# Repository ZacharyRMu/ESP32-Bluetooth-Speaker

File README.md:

# ESP32 Bluetooth Speaker with Controls

A DIY Bluetooth speaker project using an ESP32 microcontroller, a MAX98357A I²S DAC amplifier, and control buttons. Stream audio via Bluetooth A2DP, and control playback, track navigation, and volume directly from buttons.

---

## Table of Contents

- [Features](#features)  
- [Hardware Requirements](#hardware-requirements)  
- [Circuit / Wiring](#circuit--wiring)  
- [Software & Libraries](#software--libraries)  
- [Usage](#usage)  
- [Troubleshooting](#troubleshooting)  
- [Optional Enhancements](#optional-enhancements)  
- [Project Structure](#project-structure)  
- [License](#license)

---

## Features

- Bluetooth A2DP audio streaming from any compatible device (phone, computer, etc.)  
- Physical controls: play/pause, next/previous track, volume up/down  
- Uses I²S interface with MAX98357A amplifier for better audio quality  
- Configurable and extensible (add LEDs, battery, enclosures, etc.)

---

## Hardware Requirements

| Component | Description / Notes |
|---|---|
| ESP32 board | Any variant that supports Bluetooth + I²S; power via USB or external supply |
| MAX98357A I²S amplifier module | To convert digital audio to analog and drive the speaker |
| Speaker | 4 Ω or 8 Ω, approx. 3 W recommended |
| Push-buttons (×5) | For Play/Pause, Next Track, Previous Track, Volume Up, Volume Down |
| Jumper wires | For connections between ESP32, amplifier, buttons |
| Capacitor (10 µF, optional) | Between VIN and GND of amplifier to smooth power & reduce noise |
| Micro-USB cable | To program and power the ESP32 |
| Enclosure (optional) | To house the electronics nicely and safely |

---

## Circuit / Wiring

**Connections:**

- **Power**  
  - VIN on ESP32 → VIN on MAX98357A  
  - GND → GND (common ground)

- **I²S Audio Signals**  
  - I²S_BCLK (bit clock) → GPIO 27  
  - I²S_LRC (word select / left-right clock) → GPIO 14  
  - I²S_DIN (audio data) → GPIO 26  

- **Buttons** (one side of each button to GND; the other to the ESP32 GPIO pins)  
  - Play/Pause → GPIO 5  
  - Previous Track → GPIO 18  
  - Next Track → GPIO 19  
  - Volume Up → GPIO 21  
  - Volume Down → GPIO 22  

- **Optional components**  
  - 10 µF capacitor between VIN & GND at the amplifier module (reduces noise)  
  - If using amplifier shutdown / gain pins, connect per the datasheet or leave floating if unused

---

## Software & Libraries

- **Arduino IDE / PlatformIO**  
- Required libraries:  
  - [ESP32-A2DP](https://github.com/pschatzmann/ESP32-A2DP) — for Bluetooth audio sink  
  - [Arduino-Audio-Tools](https://github.com/pschatzmann/arduino-audio-tools) — for I²S & audio stream handling  

**Basic flow:**  
1. Initialize I²S stream with the given pins  
2. Start Bluetooth A2DP sink (set device name, default volume)  
3. In main loop, poll buttons with debounce logic  
4. On button presses, issue commands: play/pause, next, previous, volume up/down  

---

## Usage

1. Clone this repository.  
2. Install required libraries (Arduino IDE library manager / PlatformIO, or clone directly).  
3. Connect hardware per wiring instructions.  
4. Upload the code to the ESP32.  
5. Power it up.  
6. On your phone/computer, pair with Bluetooth device named **“ESPEAKER”** (default).  
7. Play audio and use the buttons to control playback and volume.  

---

## Troubleshooting

| Issue | Possible Cause | Solution |
|---|---|---|
| No audio / speaker silent | Wiring error; amplifier VIN not powered; ground not common | Double-check wiring; ensure amplifier module is powered; verify I²S pins match code |
| Distorted or noisy audio | Voltage supply noisy; missing capacitor; gain too high | Add the 10 µF capacitor; check amplifier gain settings; use a clean power supply |
| Buttons not responding | Wrong pins; no pull-ups; bouncing | Make sure button pins match code; use `INPUT_PULLUP` mode; implement debounce |
| BLE not pairing / not visible | Device name wrong; Bluetooth not started; power issues | Confirm `a2dp_sink.start("ESPEAKER")` runs; check ESP32’s Bluetooth functionality |

---

## Optional Enhancements

- Add battery power (for portability), e.g. LiPo + charging circuit (e.g., TP4056)  
- Enclosure: 3D-printed, wooden box, repurposed case  
- Status LEDs: indicate pairing, connected, playing state  
- RGB LEDs synced to music for visual effects  
---

## License

Specify your license here. For example: MIT License — see [LICENSE](LICENSE) file.

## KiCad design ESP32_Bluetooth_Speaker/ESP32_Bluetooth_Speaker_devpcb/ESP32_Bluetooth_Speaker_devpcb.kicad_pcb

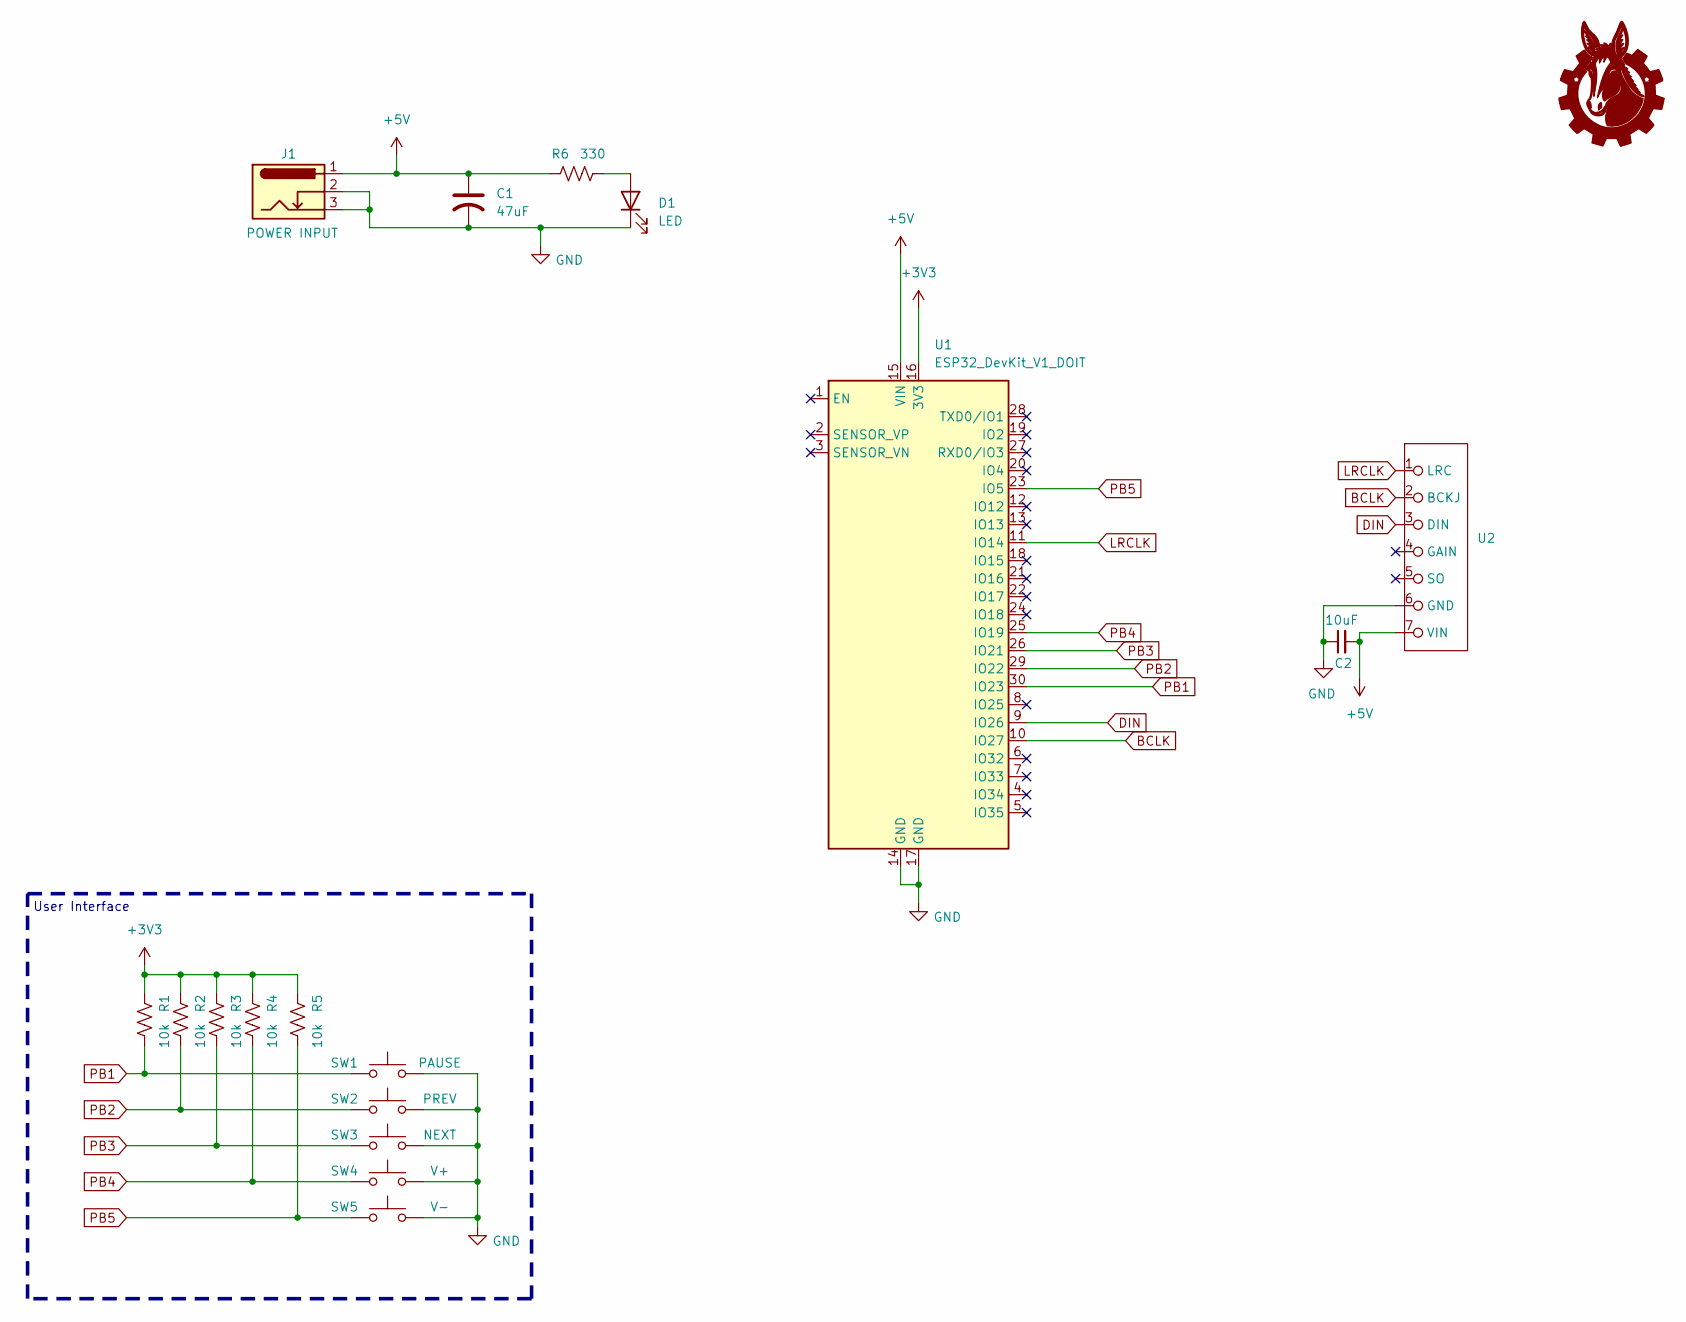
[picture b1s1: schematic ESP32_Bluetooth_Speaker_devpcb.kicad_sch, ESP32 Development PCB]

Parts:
C1: 47uF; CP_Radial_D6.3mm_P2.50mm
C2: 10uF; CP_Radial_D6.3mm_P2.50mm
D1: LED; LED_D5.0mm
J1: POWER INPUT; BarrelJack_CUI_PJ-102AH_Horizontal
R1, R2, R3, R4, R5: 10k; R_Axial_DIN0207_L6.3mm_D2.5mm_P7.62mm_Horizontal
R6: 330; R_Axial_DIN0207_L6.3mm_D2.5mm_P7.62mm_Horizontal
SW1: PAUSE; SW_Tactile_SPST_Angled_PTS645Vx58-2LFS
SW2: PREV; SW_Tactile_SPST_Angled_PTS645Vx58-2LFS
SW3: NEXT; SW_Tactile_SPST_Angled_PTS645Vx58-2LFS
SW4: V+; SW_Tactile_SPST_Angled_PTS645Vx58-2LFS
SW5: V-; SW_Tactile_SPST_Angled_PTS645Vx58-2LFS
U1: ESP32_DevKit_V1_DOIT; esp32_devkit_v1_doit
U2: PinSocket_1x07_P2.54mm_Vertical

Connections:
+3V3: R1.2, R2.2, R3.2, R4.2, R5.2, U1.16 (3V3)
+5V: C1.1, C2.2, J1.1, R6.2, U1.15 (VIN), U2.7 (VIN)
BCLK: U1.10 (IO27), U2.2 (BCKJ)
DIN: U1.9 (IO26), U2.3 (DIN)
GND: C1.2, C2.1, D1.1 (K), J1.2, J1.3, SW1.2, SW2.2, SW3.2, SW4.2, SW5.2, U1.14 (GND), U1.17 (GND), U2.6 (GND)
LRCLK: U1.11 (IO14), U2.1 (LRC)
unnamed: D1.2 (A), R6.1
PB1: R1.1, SW1.1, U1.30 (IO23)
PB2: R2.1, SW2.1, U1.29 (IO22)
PB3: R3.1, SW3.1, U1.26 (IO21)
PB4: R4.1, SW4.1, U1.25 (IO19)
PB5: R5.1, SW5.1, U1.23 (IO5)

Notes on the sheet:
User Interface

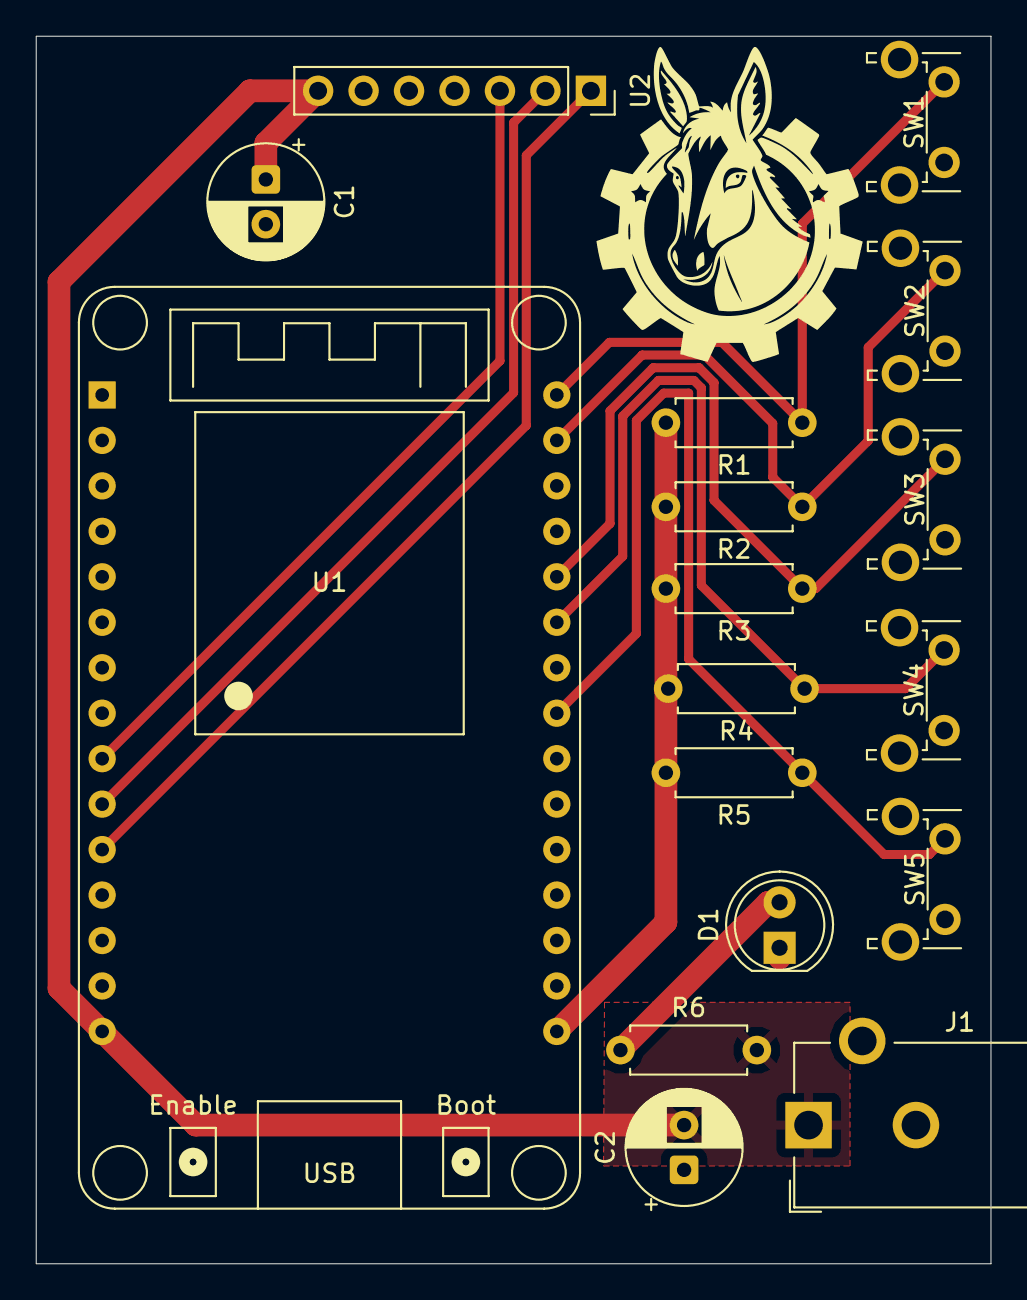
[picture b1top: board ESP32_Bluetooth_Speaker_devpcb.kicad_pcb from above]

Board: 2 copper layers, 53.3 x 68.6 mm, 17 parts (0 on the bottom side), 12 nets.

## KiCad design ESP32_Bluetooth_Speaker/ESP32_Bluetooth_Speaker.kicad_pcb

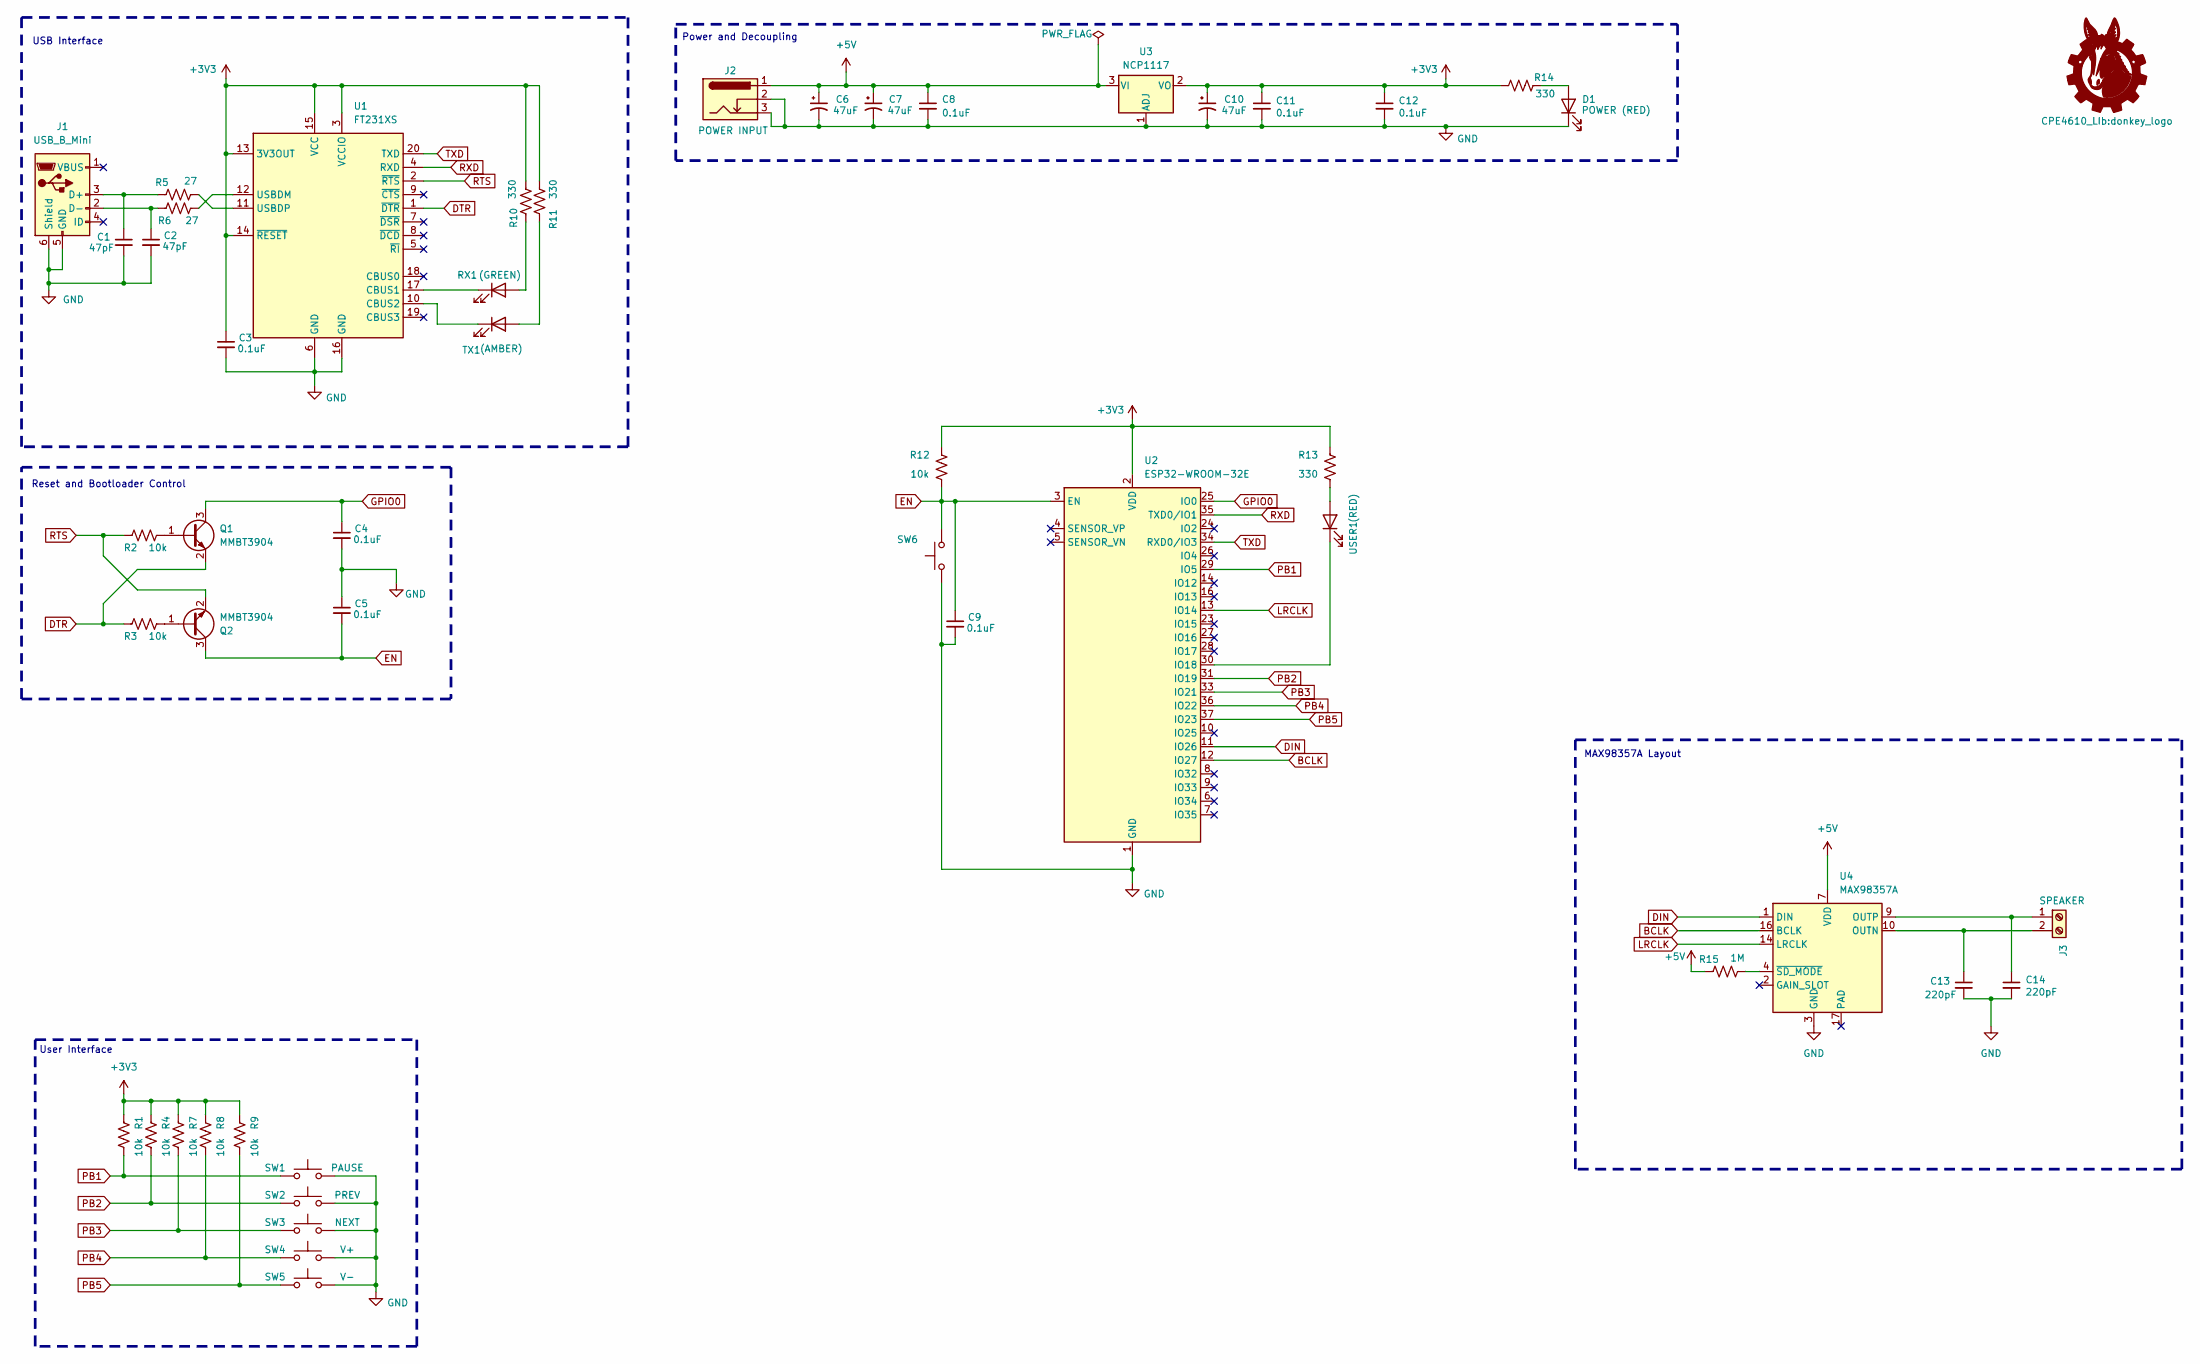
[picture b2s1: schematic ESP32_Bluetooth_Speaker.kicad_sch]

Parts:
C1, C2: 47pF; C_0805_2012Metric
C3, C4, C5, C8, C9, C11, C12: 0.1uF; C_0805_2012Metric
C6, C7, C10: 47uF; CP_Elec_6.3x5.4
C13, C14: 220pF; C_0805_2012Metric
D1: POWER (RED); LED_0805_2012Metric
J1: USB_B_Mini; USB_Mini-B_Wuerth_65100516121_Horizontal
J2: POWER INPUT; BarrelJack_CUI_PJ-102AH_Horizontal
J3: SPEAKER; TerminalBlock_RND_205-00232_1x02_P5.08mm_Horizontal
Q1, Q2: MMBT3904; SOT-23
R1, R2, R3, R4, R7, R8, R9, R12: 10k; R_0805_2012Metric
R5, R6: 27; R_0805_2012Metric
R10, R11, R13, R14: 330; R_0805_2012Metric
R15: 1M; R_0805_2012Metric
RX1: (GREEN); LED_0805_2012Metric
SW1: PAUSE; SW_Tactile_SPST_Angled_PTS645Vx58-2LFS
SW2: PREV; SW_Tactile_SPST_Angled_PTS645Vx58-2LFS
SW3: NEXT; SW_Tactile_SPST_Angled_PTS645Vx58-2LFS
SW4: V+; SW_Tactile_SPST_Angled_PTS645Vx58-2LFS
SW5: V-; SW_Tactile_SPST_Angled_PTS645Vx58-2LFS
SW6: RESET; SKQYAAE010
TX1: (AMBER); LED_0805_2012Metric
U1: FT231XS; SSOP-20_3.9x8.7mm_P0.635mm
U2: ESP32-WROOM-32E; ESP32-WROOM-32D
U3: NCP1117; TO-252-2
U4: MAX98357A; TQFN-16-1EP_3x3mm_P0.5mm_EP1.23x1.23mm
USER1: (RED); LED_0805_2012Metric

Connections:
+3V3: C3.1, C10.1, C11.1, C12.1, R1.2, R4.2, R7.2, R8.2, R9.2, R10.2, R11.2, R12.2, R13.2, R14.2, U1.3 (VCCIO), U1.13 (3V3OUT), U1.14 (~RESET), U1.15 (VCC), U2.2 (VDD), U3.2 (VO)
+5V: C6.1, C7.1, C8.1, J2.1, R15.1, U3.3 (VI), U4.7 (VDD), U4.8 (VDD)
BCLK: U2.12 (IO27), U4.16 (BCLK)
DIN: U2.11 (IO26), U4.1 (DIN)
DTR: Q1.2 (E), R3.1, U1.1 (~DTR)
EN: C5.2, C9.1, Q2.3 (C), R12.1, SW6.2, U2.3 (EN)
GND: C1.2, C2.2, C3.2, C4.2, C5.1, C6.2, C7.2, C8.2, C9.2, C10.2, C11.2, C12.2, C13.2, C14.2, D1.1 (K), J1.5 (GND), J1.6 (Shield), J2.2, J2.3, SW1.2, SW2.2, SW3.2, SW4.2, SW5.2, SW6.1, U1.6 (GND), U1.16 (GND), U2.1 (GND), U2.15 (GND), U2.38 (GND), U2.39 (GND), U3.1 (ADJ), U4.3 (GND), U4.11 (GND), U4.15 (GND)
GPIO0: C4.1, Q1.3 (C), U2.25 (IO0)
LRCLK: U2.13 (IO14), U4.14 (LRCLK)
unnamed: D1.2 (A), R14.1
unnamed: C1.1, J1.3 (D+), R5.1
unnamed: C2.1, J1.2 (D-), R6.1
unnamed: C14.1, J3.1, U4.9 (OUTP)
unnamed: C13.1, J3.2, U4.10 (OUTN)
unnamed: Q1.1 (B), R2.2
unnamed: Q2.1 (B), R3.2
unnamed: R10.1, RX1.2 (A)
unnamed: RX1.1 (K), U1.17 (CBUS1)
unnamed: R11.1, TX1.2 (A)
unnamed: TX1.1 (K), U1.10 (CBUS2)
unnamed: R6.2, U1.12 (USBDM)
unnamed: R5.2, U1.11 (USBDP)
unnamed: U2.30 (IO18), USER1.1 (K)
unnamed: R15.2, U4.4 (~SD_MODE)
unnamed: R13.1, USER1.2 (A)
PB1: R1.1, SW1.1, U2.29 (IO5)
PB2: R4.1, SW2.1, U2.31 (IO19)
PB3: R7.1, SW3.1, U2.33 (IO21)
PB4: R8.1, SW4.1, U2.36 (IO22)
PB5: R9.1, SW5.1, U2.37 (IO23)
RTS: Q2.2 (E), R2.1, U1.2 (~RTS)
RXD: U1.4 (RXD), U2.35 (TXD0/IO1)
TXD: U1.20 (TXD), U2.34 (RXD0/IO3)

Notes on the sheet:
USB Interface
Power and Decoupling
User Interface
MAX98357A Layout
Reset and Bootloader Control

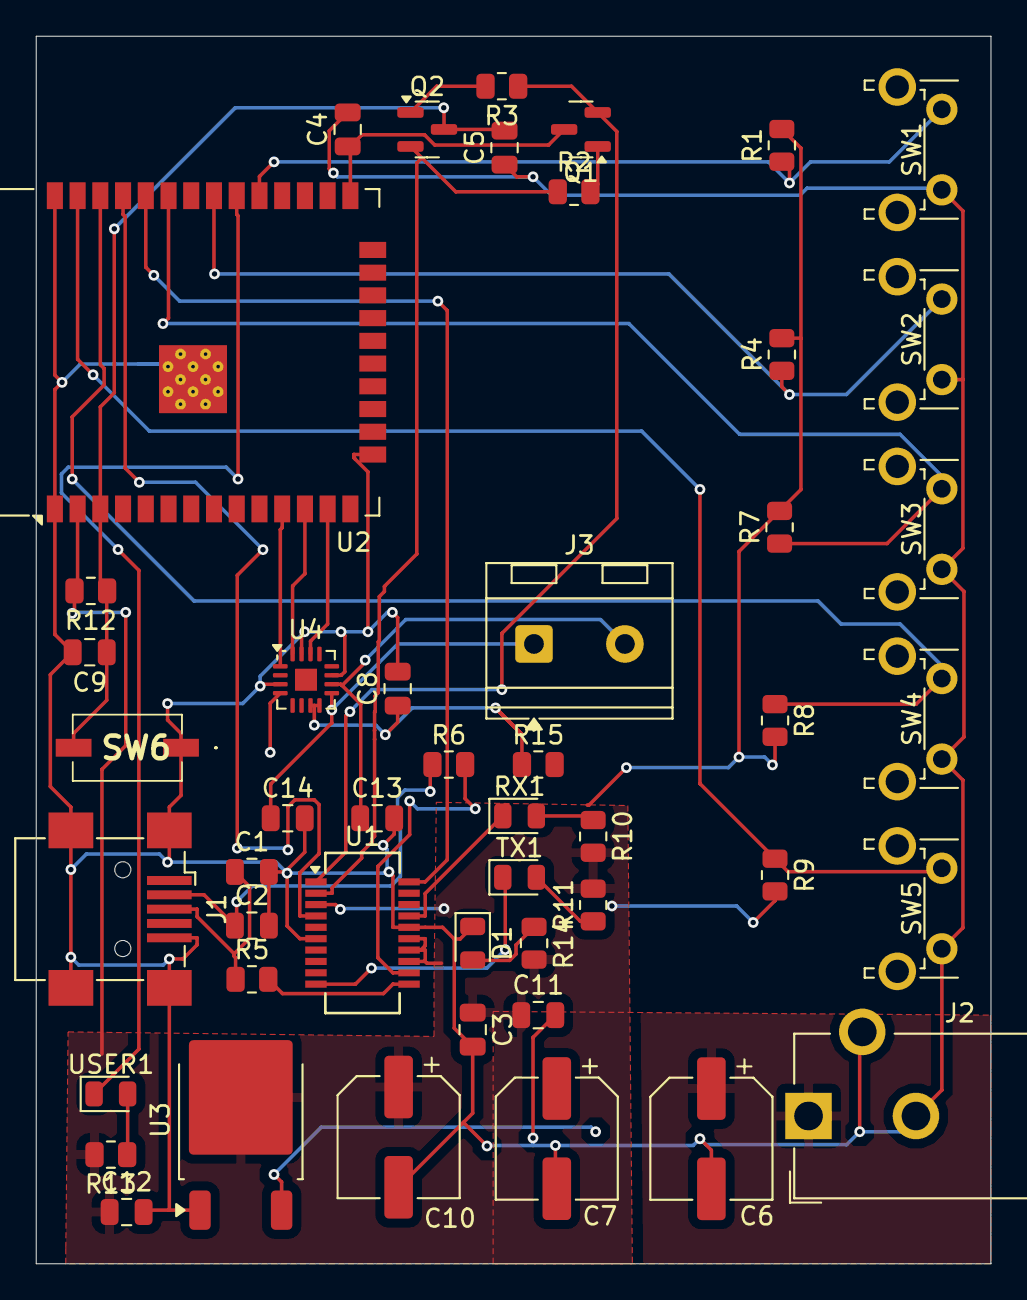
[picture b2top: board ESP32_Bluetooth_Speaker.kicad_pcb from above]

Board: 2 copper layers, 53.3 x 68.6 mm, 48 parts (0 on the bottom side), 33 nets.

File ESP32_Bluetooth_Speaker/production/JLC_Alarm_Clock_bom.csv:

Designator,Footprint,Quantity,Value,LCSC Part #
"C1, C2",0805,2,47pF,
C10_2,0805,1,10uF,
"C10, C6, C7",CP_Elec_6.3x5.4,3,47uF,
"C11_2, C11, C12, C16, C3, C4, C5, C8, C9",0805,9,0.1uF,
"C13, C14",0805,2,220pF,
D1,0805,1,POWER (RED),
J2,BarrelJack_CUI_PJ-102AH_Horizontal,1,POWER INPUT,
"Q1, Q2",SOT-23,2,MMBT3904,
"R1, R12, R2, R3, R4, R7, R8, R9",0805,8,10k,
"R10, R11, R13, R14",0805,4,330,
R15,0805,1,1M,
"R5, R6",0805,2,27,
RX1,0805,1,(GREEN),
SPEAKER,TerminalBlock_RND_205-00232_1x02_P5.08mm_Horizontal,1,SPEAKER,
SW1,SW_Tactile_SPST_Angled_PTS645Vx58-2LFS,1,PAUSE,
SW2,SW_Tactile_SPST_Angled_PTS645Vx58-2LFS,1,PREV,
SW3,SW_Tactile_SPST_Angled_PTS645Vx58-2LFS,1,NEXT,
SW4,SW_Tactile_SPST_Angled_PTS645Vx58-2LFS,1,V+,
SW5,SW_Tactile_SPST_Angled_PTS645Vx58-2LFS,1,V-,
SW6,SKQYAAE010,1,RESET,
TX1,0805,1,(AMBER),
U1,SSOP-20_3.9x8.7mm_P0.635mm,1,FT231XS,
U2,ESP32-WROOM-32D,1,ESP32-WROOM-32E,
U3,TO-252-2,1,NCP1117,
U4,TQFN-16-1EP_3x3mm_P0.5mm_EP1.23x1.23mm,1,MAX98357A,
USB,USB_Mini-B_Wuerth_65100516121_Horizontal,1,USB_B_Mini,
USER1,0805,1,(RED),

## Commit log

2025-09-19 Updated README.
2025-09-19 Created Software outline + code from development process. Added 3D CAD speaker enclosure.
2025-09-19 Added .gitignore.
2025-09-19 Added 3D enclosure.
2025-09-19 modified .DS_store.
2025-09-19 Started Schematic capture for PCB.
2025-09-20 Idk what this is
2026-01-18 Initial Commit for Project
2026-01-18 Created schematic and PCB.
2026-03-21 Created dev PCB + model
2026-03-22 ESP32 Code + initial code rev
2026-03-23 Added CAD assembly and surface mount PCB initial rev
